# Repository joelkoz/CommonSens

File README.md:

# CommonSens
A collection of ready to use Signal K devices

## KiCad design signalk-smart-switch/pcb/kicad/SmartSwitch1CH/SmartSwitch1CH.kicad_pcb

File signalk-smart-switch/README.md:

# SensESP Smart Switches

This project is used to compile SensESP smart switch firmware to an ESPxx powered device with power control via relays or MOSFETs

Loading this project into PlatformIO, there are five different devices that this project can be built for:

1. sonoff4ch
1. shelly1
1. shelly25
1. m5stick-c
1. common_sense_d1_mini

Once opened in PlatformIO, go to the "Project Tasks" tab (the icon with the alien face), drop down the device you are building for, and select "Build", "Upload", or "Upload and Monitor".

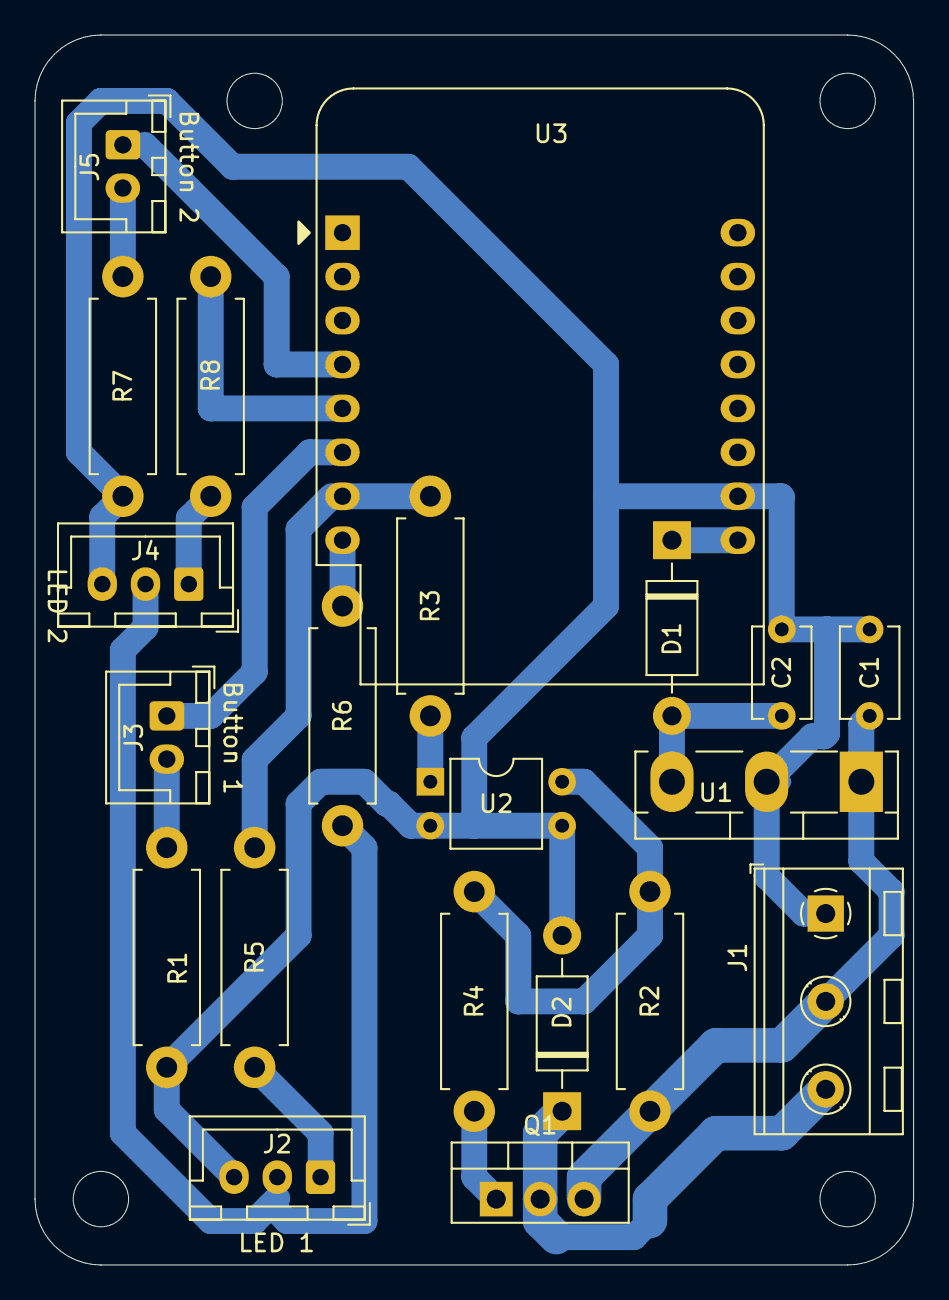
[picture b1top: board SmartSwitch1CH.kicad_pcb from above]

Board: 2 copper layers, 50.8 x 71.1 mm, 21 parts (0 on the bottom side), 18 nets.

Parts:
C1: 0.33uf; C_Disc_D5.1mm_W3.2mm_P5.00mm
C2: 0.1uf; C_Disc_D5.1mm_W3.2mm_P5.00mm
D1: 1N4001; D_DO-41_SOD81_P10.16mm_Horizontal
D2: 1N4007; D_DO-41_SOD81_P10.16mm_Horizontal
J1: Screw_Terminal_01x03; TerminalBlock_RND_205-00233_1x03_P5.08mm_Horizontal
J2: Button1 LED; JST_XH_B3B-XH-A_1x03_P2.50mm_Vertical
J3: Button1 Input; JST_XH_B2B-XH-A_1x02_P2.50mm_Vertical
J4: Button2 LED; JST_XH_B3B-XH-A_1x03_P2.50mm_Vertical
J5: Button2 Input; JST_XH_B2B-XH-A_1x02_P2.50mm_Vertical
Q1: IRF4905; TO-220-3_Vertical
R1, R2, R7: 10k; R_Axial_DIN0411_L9.9mm_D3.6mm_P12.70mm_Horizontal
R3: 220R; R_Axial_DIN0411_L9.9mm_D3.6mm_P12.70mm_Horizontal
R4: 1k; R_Axial_DIN0411_L9.9mm_D3.6mm_P12.70mm_Horizontal
R5, R8: 470R; R_Axial_DIN0411_L9.9mm_D3.6mm_P12.70mm_Horizontal
R6: 10K; R_Axial_DIN0411_L9.9mm_D3.6mm_P12.70mm_Horizontal
U1: L7805; TO-218-3_Vertical
U2: PC817; DIP-4_W7.62mm
U3: WeMos_D1_mini; WEMOS_D1_mini_light

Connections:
+3V3: R6.1, U3.8
+5V: D1.1, U3.9
+24V: C1.1, J1.2, Q1.3, R2.2, U1.1
Button1: J3.1, U3.6
Button2: J5.1, U3.4
GND: C1.2, C2.2, D2.2, J1.1, J2.3, J4.3, R1.2, R7.2, U1.2, U2.2, U2.3, U3.10
Load1: D2.1, J1.3, Q1.2
unnamed: C2.1, D1.2, U1.3
unnamed: J2.1, R5.2
unnamed: J3.2, R1.1
unnamed: J4.1, R8.2
unnamed: J5.2, R7.1
unnamed: Q1.1, R4.2
unnamed: R2.1, R4.1, U2.4
unnamed: R3.2, U2.1
PowerLed: J2.2, J4.2, R6.2
Relay1: R3.1, R5.1, U3.7
Relay2: R8.1, U3.5

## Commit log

2021-04-01 Update .gitignore
    Ignore common PlatformIO directories
2021-04-01 Initial SmartSwitch code
    Initial checkin of SmartSwitch code.
2021-11-25 Updated .gitignore
2021-11-25 Added KiCad files for reference board
